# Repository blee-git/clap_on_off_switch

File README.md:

# Clap-clap on-off switch

## Single pulse generation from two consecutive pulses: signal processing and windowing

## Version 1.0

Only signal processing section of the circuit board (black silk screened PCB) is usable since circuit diagram is lost.

## Version 1.1

## Next version

## Pulse windowing logic implemented in an MCU (Arduino, etc)

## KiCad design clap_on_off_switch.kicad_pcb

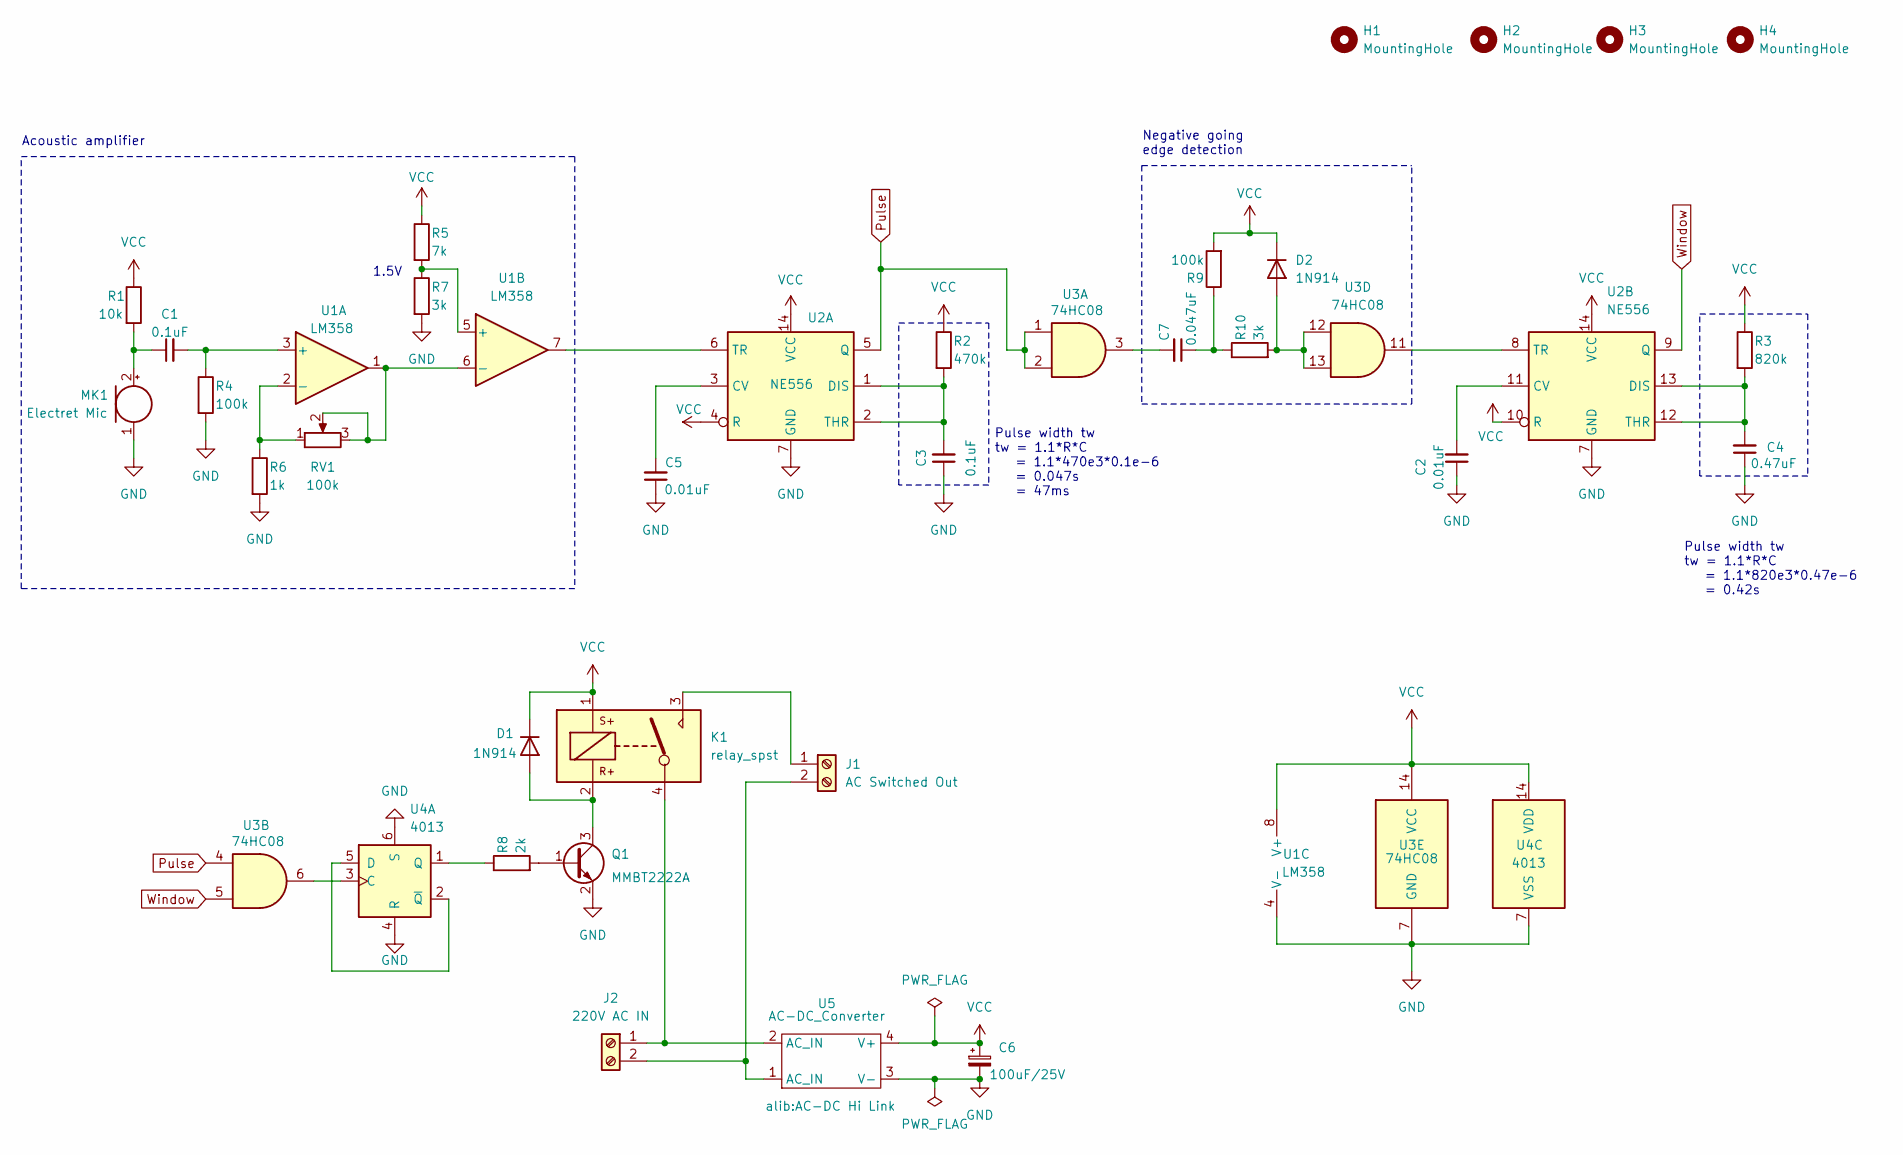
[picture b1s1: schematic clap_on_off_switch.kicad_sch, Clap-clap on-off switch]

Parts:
C1, C3: 0.1uF; C_0805_2012Metric_Pad1.18x1.45mm_HandSolder
C2, C5: 0.01uF; C_0805_2012Metric_Pad1.18x1.45mm_HandSolder
C4: 0.47uF; C_0805_2012Metric_Pad1.18x1.45mm_HandSolder
C6: 100uF/25V; CP_Radial_D6.3mm_P2.50mm
C7: 0.047uF; C_0805_2012Metric_Pad1.18x1.45mm_HandSolder
D1, D2: 1N914; D_0805_2012Metric_Pad1.15x1.40mm_HandSolder
H1, H2, H3, H4: MountingHole; MountingHole_3.2mm_M3
J1: AC Switched Out; TestPoint_2Pads_Pitch5.08mm_Drill1.3mm
J2: 220V AC IN; TestPoint_2Pads_Pitch5.08mm_Drill1.3mm
K1: relay_spst; Relay_Omron
MK1: Electret Mic; Electret Microphone FQ-003
Q1: MMBT2222A; SOT-23
R1: 10k; R_0805_2012Metric_Pad1.20x1.40mm_HandSolder
R2: 470k; R_0805_2012Metric_Pad1.20x1.40mm_HandSolder
R3: 820k; R_0805_2012Metric_Pad1.20x1.40mm_HandSolder
R4, R9: 100k; R_0805_2012Metric_Pad1.20x1.40mm_HandSolder
R5: 7k; R_0805_2012Metric_Pad1.20x1.40mm_HandSolder
R6: 1k; R_0805_2012Metric_Pad1.20x1.40mm_HandSolder
R7, R10: 3k; R_0805_2012Metric_Pad1.20x1.40mm_HandSolder
R8: 2k; R_0805_2012Metric_Pad1.20x1.40mm_HandSolder
RV1: 100k; Potentiometer_Bourns_3005_Horizontal
U1: LM358; SO-8_5.3x6.2mm_P1.27mm
U2: NE556; SO-14_5.3x10.2mm_P1.27mm
U3: 74HC08; SOIC-14_3.9x8.7mm_P1.27mm
U4: 4013; SOIC-14_3.9x8.7mm_P1.27mm
U5: AC-DC_Converter; AC-DC Hi Link

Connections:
GND: C2.1, C3.1, C4.1, C5.1, C6.2, MK1.1 (-), Q1.2 (E), R4.2, R6.2, R7.2, U1.4 (V-), U2.7 (GND), U3.7 (GND), U4.4 (R), U4.6 (S), U4.7 (VSS), U5.3 (V-)
unnamed: C7.1, R9.1, R10.1
unnamed: C7.2, U3.3
unnamed: D1.2 (A), K1.2, Q1.3 (C)
unnamed: D2.2 (A), R10.2, U3.12, U3.13
unnamed: J1.1, K1.3
unnamed: J1.2, J2.2, U5.1 (AC_IN)
unnamed: J2.1, K1.4, U5.2 (AC_IN)
unnamed: C1.1, MK1.2 (+), R1.2
unnamed: Q1.1 (B), R8.2
unnamed: C1.2, R4.1, U1.3 (+)
unnamed: R6.1, RV1.1, U1.2 (-)
unnamed: R5.2, R7.1, U1.5 (+)
unnamed: RV1.2, RV1.3, U1.1, U1.6 (-)
unnamed: C5.2, U2.3 (CV)
unnamed: C3.2, R2.2, U2.1 (DIS), U2.2 (THR)
unnamed: U1.7, U2.6 (TR)
unnamed: C2.2, U2.11 (CV)
unnamed: C4.2, R3.2, U2.12 (THR), U2.13 (DIS)
unnamed: U2.8 (TR), U3.11
unnamed: U3.6, U4.3 (C)
unnamed: U4.2 (~Q), U4.5 (D)
unnamed: R8.1, U4.1 (Q)
Pulse: U2.5 (Q), U3.1, U3.2, U3.4
VCC: C6.1, D1.1 (K), D2.1 (K), K1.1, R1.1, R2.1, R3.1, R5.1, R9.2, U1.8 (V+), U2.4 (R), U2.10 (R), U2.14 (VCC), U3.14 (VCC), U4.14 (VDD), U5.4 (V+)
Window: U2.9 (Q), U3.5

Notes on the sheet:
Pulse width tw tw = 1.1*R*C = 1.1*820e3*0.47e-6 = 0.42s
Pulse width tw tw = 1.1*R*C = 1.1*470e3*0.1e-6 = 0.047s = 47ms
1.5V
Negative going edge detection
Acoustic amplifier

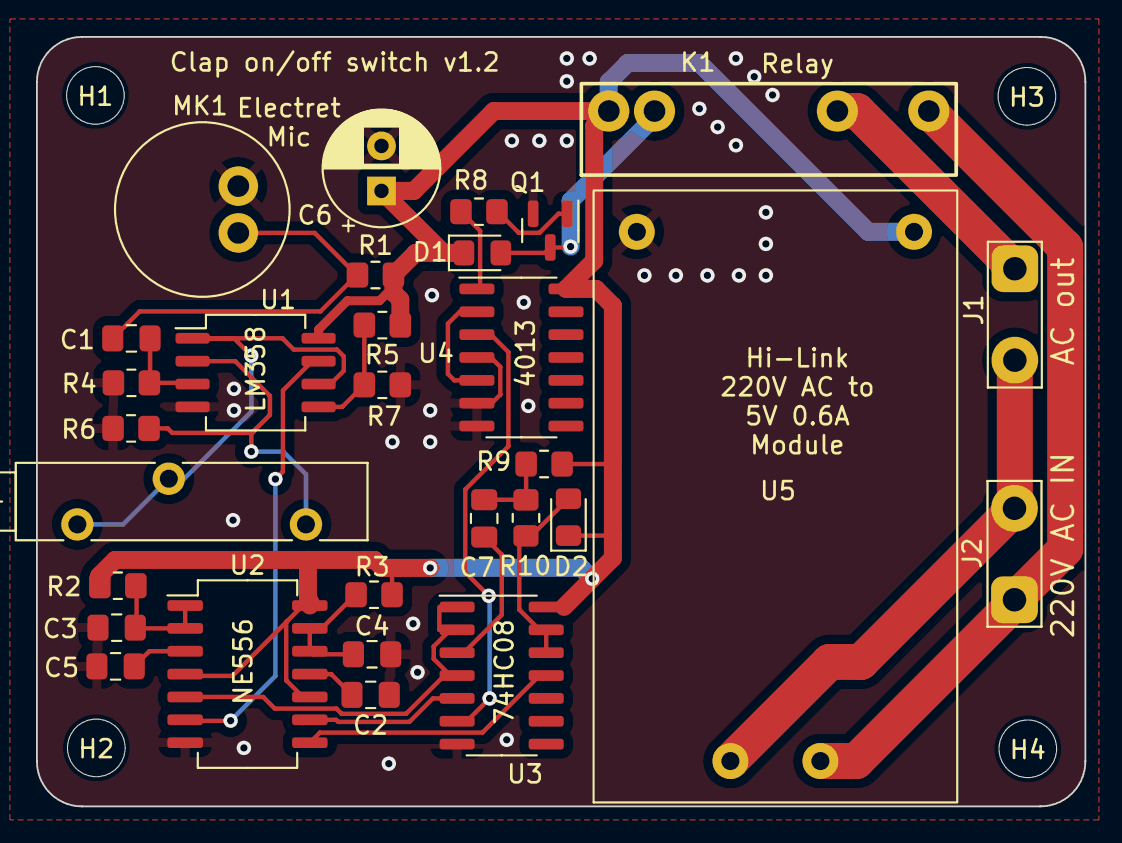
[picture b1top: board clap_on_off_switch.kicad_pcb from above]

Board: 2 copper layers, 58.2 x 42.8 mm, 34 parts (0 on the bottom side), 26 nets.

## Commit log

2025-02-07 Initial upload
2025-02-07 PATCH: .gitignore is added
2025-02-07 README.md modified
